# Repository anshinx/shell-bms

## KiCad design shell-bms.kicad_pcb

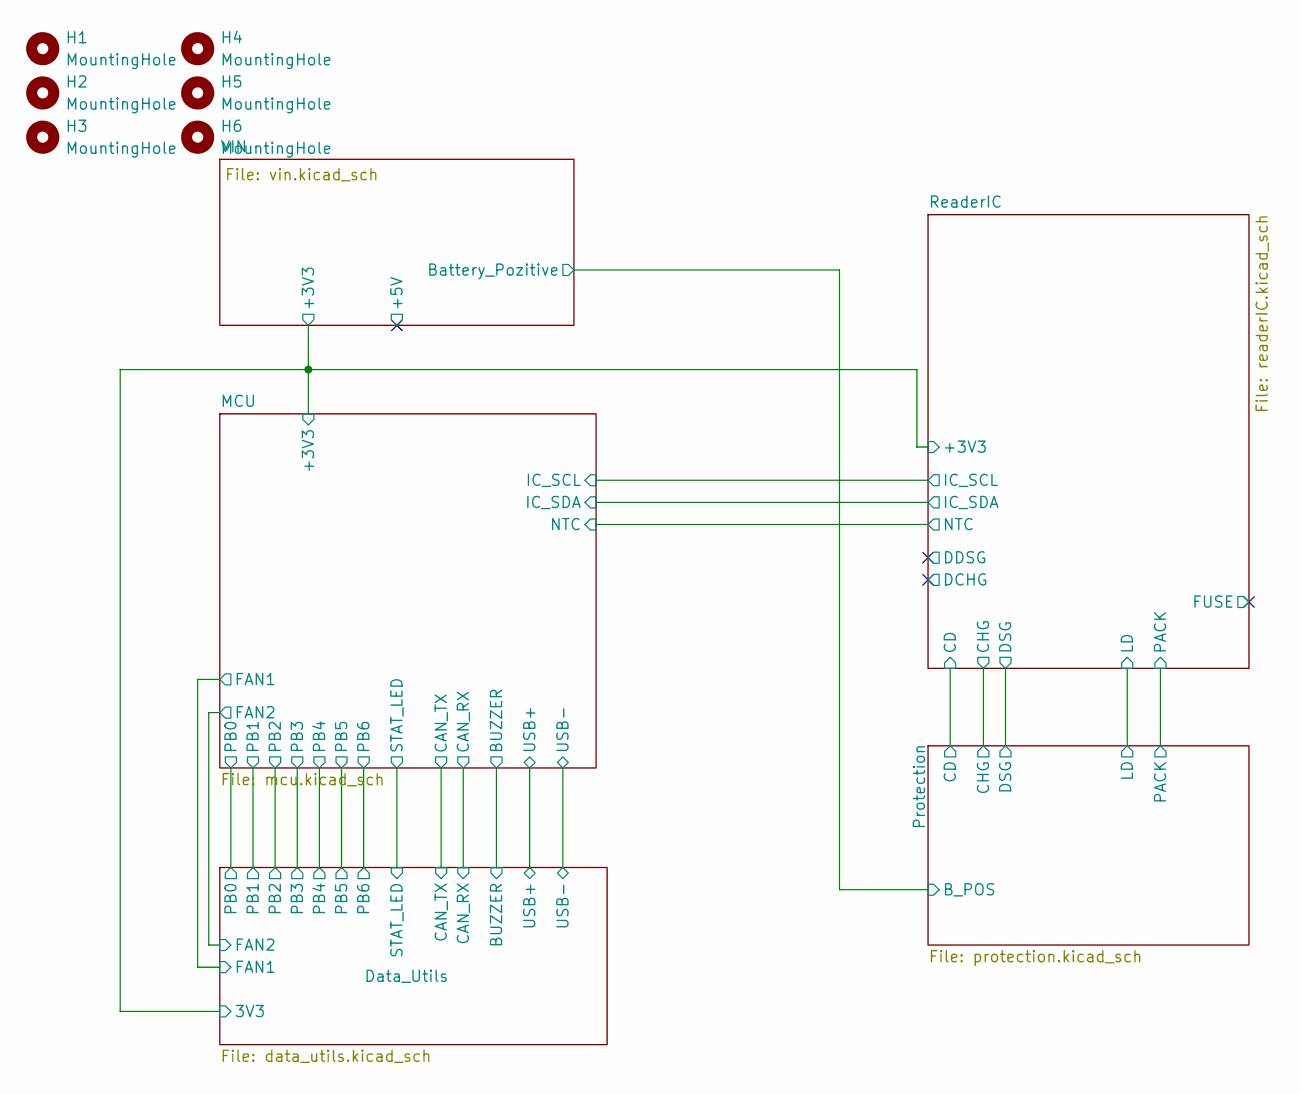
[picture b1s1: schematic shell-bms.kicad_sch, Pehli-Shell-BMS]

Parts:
H1, H2, H3, H4, H5, H6: MountingHole; Mounting_Wuerth_WA-SMST-2.25mm_H2.5mm_9774025943

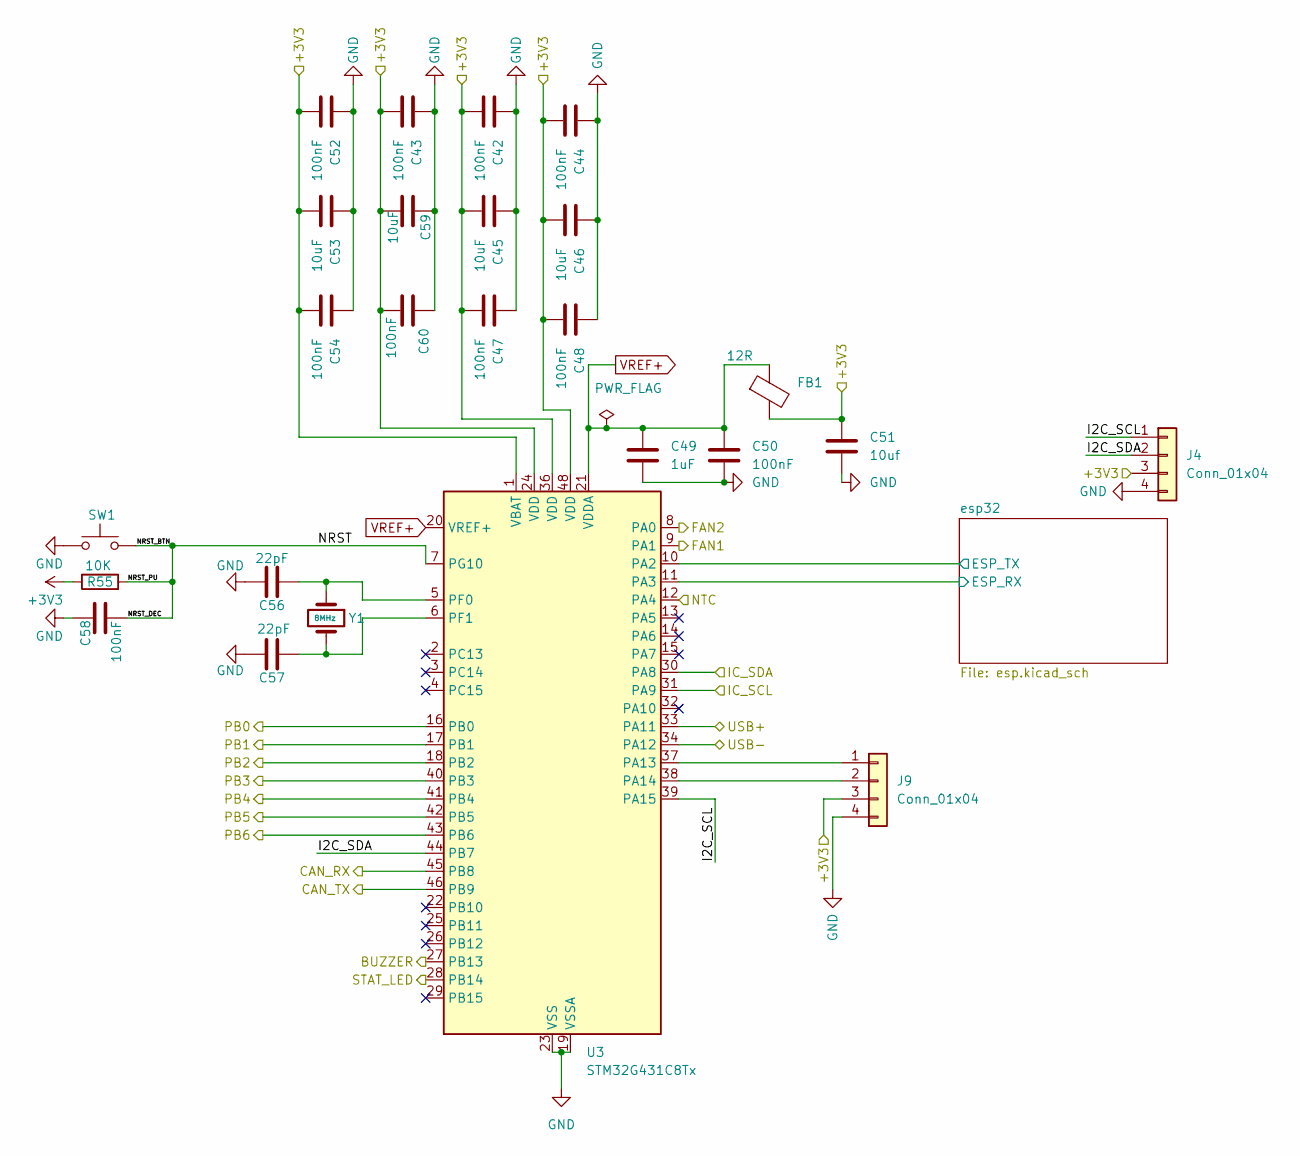
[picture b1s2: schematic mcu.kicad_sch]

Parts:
C42, C43, C44, C47, C48, C50, C52, C54, C60: 100nF; C_0603_1608Metric_Pad1.08x0.95mm_HandSolder
C45, C46, C53, C59: 10uF; C_0603_1608Metric_Pad1.08x0.95mm_HandSolder
C49: 1uF; C_0603_1608Metric_Pad1.08x0.95mm_HandSolder
C51: 10uf; C_0805_2012Metric_Pad1.18x1.45mm_HandSolder
C56, C57: 22pF; C_0603_1608Metric_Pad1.08x0.95mm_HandSolder
C58: 100nF; C_Disc_D10.5mm_W5.0mm_P5.00mm
FB1: 12R; R_0805_2012Metric_Pad1.20x1.40mm_HandSolder
J4, J9: Conn_01x04; PinSocket_1x04_P2.00mm_Vertical
R55: 10K; R_Axial_DIN0207_L6.3mm_D2.5mm_P7.62mm_Horizontal
SW1: SW_Push; SW_PUSH_6mm_H8mm
U3: STM32G431C8Tx; LQFP-48_7x7mm_P0.5mm
Y1: 8MHz; Crystal_HC18-U_Vertical

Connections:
+3V3: C42.2, C43.2, C44.2, C45.2, C46.2, C47.2, C48.2, C51.1, C52.2, C53.2, C54.2, C59.2, C60.2, FB1.2, J4.3, J9.3, R55.2, U3.1 (VBAT), U3.24 (VDD), U3.36 (VDD), U3.48 (VDD); also elsewhere on the board
/Data_Utils/BUZZER: U3.27 (PB13); also elsewhere on the board
/Data_Utils/CAN_RX: U3.45 (PB8); also elsewhere on the board
/Data_Utils/CAN_TX: U3.46 (PB9); also elsewhere on the board
/Data_Utils/FAN1: U3.9 (PA1); also elsewhere on the board
/Data_Utils/FAN2: U3.8 (PA0); also elsewhere on the board
/Data_Utils/PB0: U3.16 (PB0); also elsewhere on the board
/Data_Utils/PB1: U3.17 (PB1); also elsewhere on the board
/Data_Utils/PB2: U3.18 (PB2); also elsewhere on the board
/Data_Utils/PB3: U3.40 (PB3); also elsewhere on the board
/Data_Utils/PB4: U3.41 (PB4); also elsewhere on the board
/Data_Utils/PB5: U3.42 (PB5); also elsewhere on the board
/Data_Utils/PB6: U3.43 (PB6); also elsewhere on the board
/Data_Utils/STAT_LED: U3.28 (PB14); also elsewhere on the board
/Data_Utils/USB+: U3.33 (PA11); also elsewhere on the board
/Data_Utils/USB-: U3.34 (PA12); also elsewhere on the board
/MCU/I2C_SCL: J4.1, U3.39 (PA15)
/MCU/I2C_SDA: J4.2, U3.44 (PB7)
/MCU/IC_SCL: U3.31 (PA9); also elsewhere on the board
/MCU/IC_SDA: U3.30 (PA8); also elsewhere on the board
/MCU/NRST: C58.2, R55.1, SW1.2, U3.7 (PG10)
/MCU/NTC: U3.12 (PA4); also elsewhere on the board
/MCU/esp32/ESP_RX: U3.11 (PA3); also elsewhere on the board
/MCU/esp32/ESP_TX: U3.10 (PA2); also elsewhere on the board
GND: C42.1, C43.1, C44.1, C45.1, C46.1, C47.1, C48.1, C49.2, C50.2, C51.2, C52.1, C53.1, C54.1, C56.1, C57.1, C58.1, C59.1, C60.1, J4.4, J9.4, SW1.1, U3.19 (VSSA), U3.23 (VSS), U3.35 (VSS), U3.47 (VSS); also elsewhere on the board
unnamed: J9.1, U3.37 (PA13)
unnamed: J9.2, U3.38 (PA14)
unnamed: C56.2, U3.5 (PF0), Y1.1
unnamed: C57.2, U3.6 (PF1), Y1.2
VREF+: C49.1, C50.1, FB1.1, U3.20 (VREF+), U3.21 (VDDA)

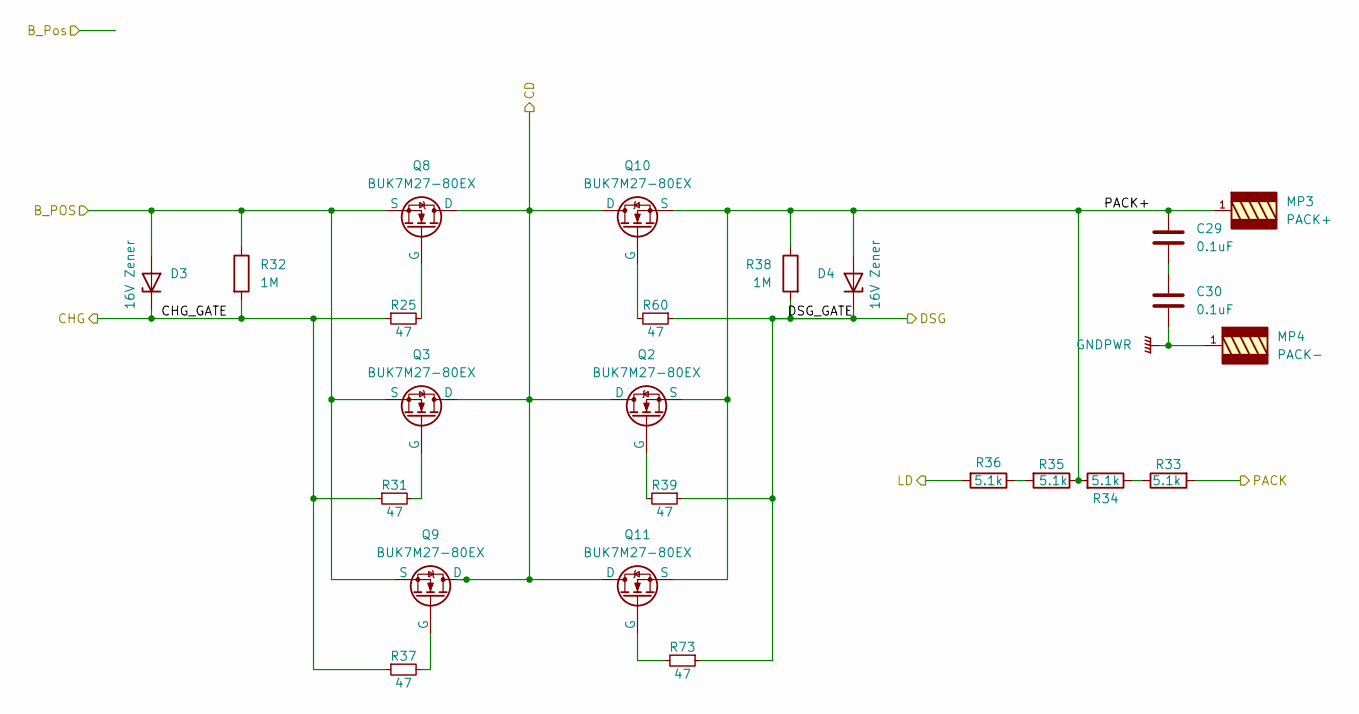
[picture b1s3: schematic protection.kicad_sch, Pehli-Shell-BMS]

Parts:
C29, C30: 0.1uF; C_0805_2012Metric_Pad1.18x1.45mm_HandSolder
D3, D4: 16V Zener; D_SMF
MP3: PACK+; WP-BUTR_7460307
MP4: PACK-; WP-BUTR_7460307
Q2, Q3, Q8, Q9, Q10, Q11: BUK7M27-80EX; LFPAK33
R25, R31, R37, R39, R60, R73: 47; R_0603_1608Metric_Pad0.98x0.95mm_HandSolder; PartNumber RC0603FR-0747RL
R32, R38: 1M; R_2512_6332Metric_Pad1.40x3.35mm_HandSolder
R33, R34, R35, R36: 5.1k; R_0603_1608Metric_Pad0.98x0.95mm_HandSolder

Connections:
/Protection/B_POS: D3.2 (A), Q3.1 (S), Q3.2 (S), Q3.3 (S), Q8.1 (S), Q8.2 (S), Q8.3 (S), Q9.1 (S), Q9.2 (S), Q9.3 (S), R32.1; also elsewhere on the board
/Protection/CD: Q2.5 (D), Q3.5 (D), Q8.5 (D), Q9.5 (D), Q10.5 (D), Q11.5 (D); also elsewhere on the board
/Protection/CHG_GATE: D3.1 (K), R25.1, R31.1, R32.2, R37.1; also elsewhere on the board
/Protection/DSG_GATE: D4.1 (K), R38.2, R39.1, R60.1, R73.1; also elsewhere on the board
/Protection/LD: R36.2; also elsewhere on the board
/Protection/PACK: R33.2; also elsewhere on the board
/Protection/PACK+: C29.1, D4.2 (A), MP3.1, MP3.2, MP3.3, MP3.4, MP3.5, MP3.6, MP3.7, MP3.8, Q2.1 (S), Q2.2 (S), Q2.3 (S), Q10.1 (S), Q10.2 (S), Q10.3 (S), Q11.1 (S), Q11.2 (S), Q11.3 (S), R34.2, R35.1, R38.1
GNDPWR: C30.2, MP4.1, MP4.2, MP4.3, MP4.4, MP4.5, MP4.6, MP4.7, MP4.8; also elsewhere on the board
unnamed: C29.2, C30.1
unnamed: Q2.4 (G), R39.2
unnamed: Q3.4 (G), R31.2
unnamed: Q8.4 (G), R25.2
unnamed: Q9.4 (G), R37.2
unnamed: Q10.4 (G), R60.2
unnamed: Q11.4 (G), R73.2
unnamed: R33.1, R34.1
unnamed: R35.2, R36.1

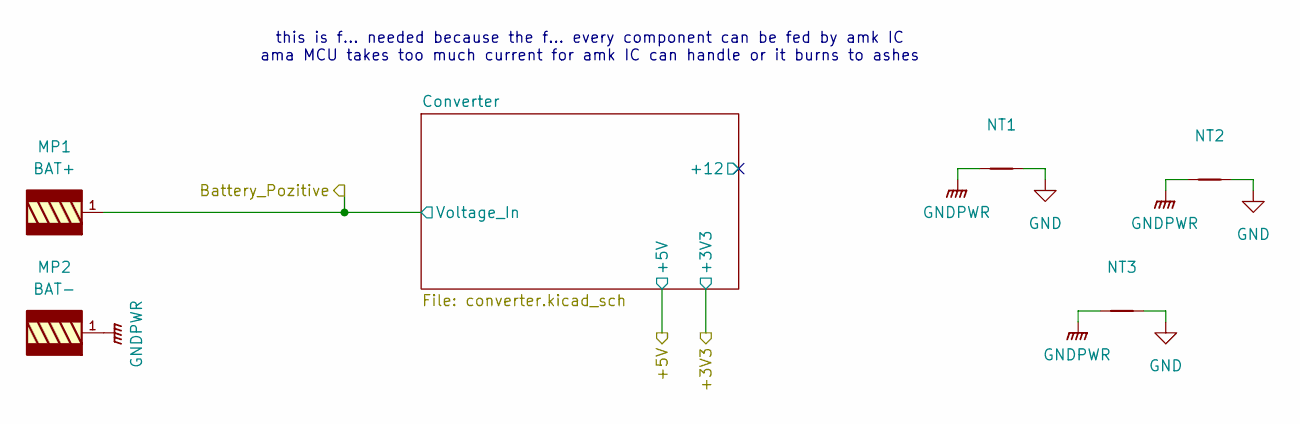
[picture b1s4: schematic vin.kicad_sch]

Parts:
MP1: BAT+; WP-BUTR_7460307
MP2: BAT-; WP-BUTR_7460307
NT1, NT2, NT3: NetTie_2; NetTie-2_THT_Pad0.3mm

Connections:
/Protection/B_POS: MP1.1, MP1.2, MP1.3, MP1.4, MP1.5, MP1.6, MP1.7, MP1.8; also elsewhere on the board
GND: NT1.2, NT2.2, NT3.2; also elsewhere on the board
GNDPWR: MP2.1, MP2.2, MP2.3, MP2.4, MP2.5, MP2.6, MP2.7, MP2.8, NT1.1, NT2.1, NT3.1; also elsewhere on the board

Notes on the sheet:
this is f... needed because the f... every component can be fed by amk IC ama MCU takes too much current for amk IC can handle or it burns to ashes

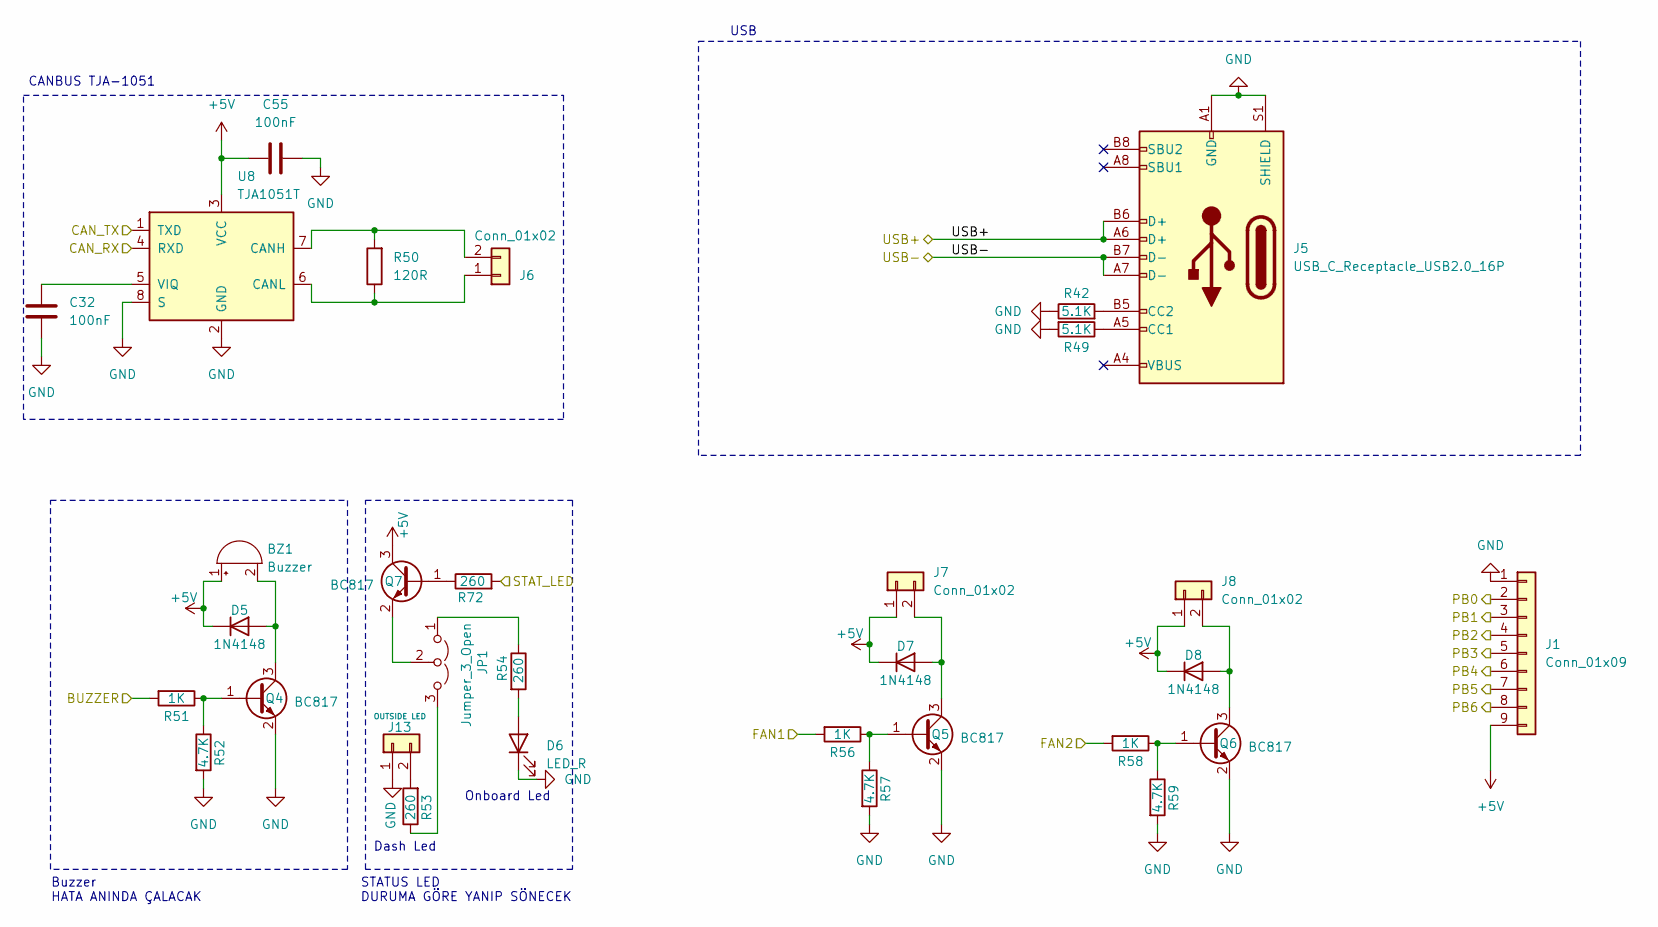
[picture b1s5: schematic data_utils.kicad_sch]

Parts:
BZ1: Buzzer; Buzzer_12x9.5RM7.6
C32: 100nF; C_0603_1608Metric_Pad1.08x0.95mm_HandSolder
C55: 100nF; C_1210_3225Metric_Pad1.33x2.70mm_HandSolder
D5, D7, D8: 1N4148; D_DO-35_SOD27_P7.62mm_Horizontal
D6: LED_R; LED_D1.8mm_W3.3mm_H2.4mm
J1: Conn_01x09; PinSocket_1x09_P2.54mm_Vertical
J5: USB_C_Receptacle_USB2.0_16P; USB_C_Receptacle_HCTL_HC-TYPE-C-16P-01A
J6: Conn_01x02; PinSocket_1x02_P2.00mm_Horizontal
J7, J8: Conn_01x02; PinSocket_1x02_P2.00mm_Vertical
J13: OUTSIDE LED; PinSocket_1x02_P2.00mm_Horizontal
JP1: Jumper_3_Open; PinHeader_1x03_P1.27mm_Vertical
Q4, Q5, Q6, Q7: BC817; SOT-23
R42, R49: 5.1K; R_0603_1608Metric_Pad0.98x0.95mm_HandSolder
R50: 120R; R_0603_1608Metric_Pad0.98x0.95mm_HandSolder
R51, R56, R58: 1K; R_1210_3225Metric_Pad1.30x2.65mm_HandSolder
R52, R57, R59: 4.7K; R_1210_3225Metric_Pad1.30x2.65mm_HandSolder
R53, R54, R72: 260; R_1210_3225Metric_Pad1.30x2.65mm_HandSolder
U8: TJA1051T; SOIC-8_3.9x4.9mm_P1.27mm

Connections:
+5V: BZ1.1 (+), C55.1, D5.1 (K), D7.1 (K), D8.1 (K), J1.9, J7.1, J8.1, Q7.3 (C), U8.3 (VCC); also elsewhere on the board
/Data_Utils/BUZZER: R51.2; also elsewhere on the board
/Data_Utils/CAN_RX: U8.4 (RXD); also elsewhere on the board
/Data_Utils/CAN_TX: U8.1 (TXD); also elsewhere on the board
/Data_Utils/FAN1: R56.2; also elsewhere on the board
/Data_Utils/FAN2: R58.2; also elsewhere on the board
/Data_Utils/PB0: J1.2; also elsewhere on the board
/Data_Utils/PB1: J1.3; also elsewhere on the board
/Data_Utils/PB2: J1.4; also elsewhere on the board
/Data_Utils/PB3: J1.5; also elsewhere on the board
/Data_Utils/PB4: J1.6; also elsewhere on the board
/Data_Utils/PB5: J1.7; also elsewhere on the board
/Data_Utils/PB6: J1.8; also elsewhere on the board
/Data_Utils/STAT_LED: R72.2; also elsewhere on the board
/Data_Utils/USB+: J5.A6 (D+), J5.B6 (D+); also elsewhere on the board
/Data_Utils/USB-: J5.A7 (D-), J5.B7 (D-); also elsewhere on the board
GND: C32.2, C55.2, D6.1 (K), J1.1, J5.A1 (GND), J5.A12 (GND), J5.B1 (GND), J5.B12 (GND), J5.S1 (SHIELD), J13.1, Q4.2 (E), Q5.2 (E), Q6.2 (E), R42.1, R49.2, R52.2, R57.2, R59.2, U8.2 (GND), U8.8 (S); also elsewhere on the board
unnamed: BZ1.2 (-), D5.2 (A), Q4.3 (C)
unnamed: D6.2 (A), R54.2
unnamed: D7.2 (A), J7.2, Q5.3 (C)
unnamed: D8.2 (A), J8.2, Q6.3 (C)
unnamed: J5.A5 (CC1), R49.1
unnamed: J5.B5 (CC2), R42.2
unnamed: J6.1, R50.1, U8.6 (CANL)
unnamed: J6.2, R50.2, U8.7 (CANH)
unnamed: J13.2, R53.2
unnamed: JP1.1 (A), R54.1
unnamed: JP1.3 (B), R53.1
unnamed: JP1.2 (C), Q7.2 (E)
unnamed: Q4.1 (B), R51.1, R52.1
unnamed: Q5.1 (B), R56.1, R57.1
unnamed: Q6.1 (B), R58.1, R59.1
unnamed: Q7.1 (B), R72.1
unnamed: C32.1, U8.5 (VIQ)

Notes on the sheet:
Buzzer HATA ANINDA ÇALACAK
CANBUS TJA-1051
STATUS LED DURUMA GÖRE YANIP SÖNECEK
USB
Dash Led
Onboard Led

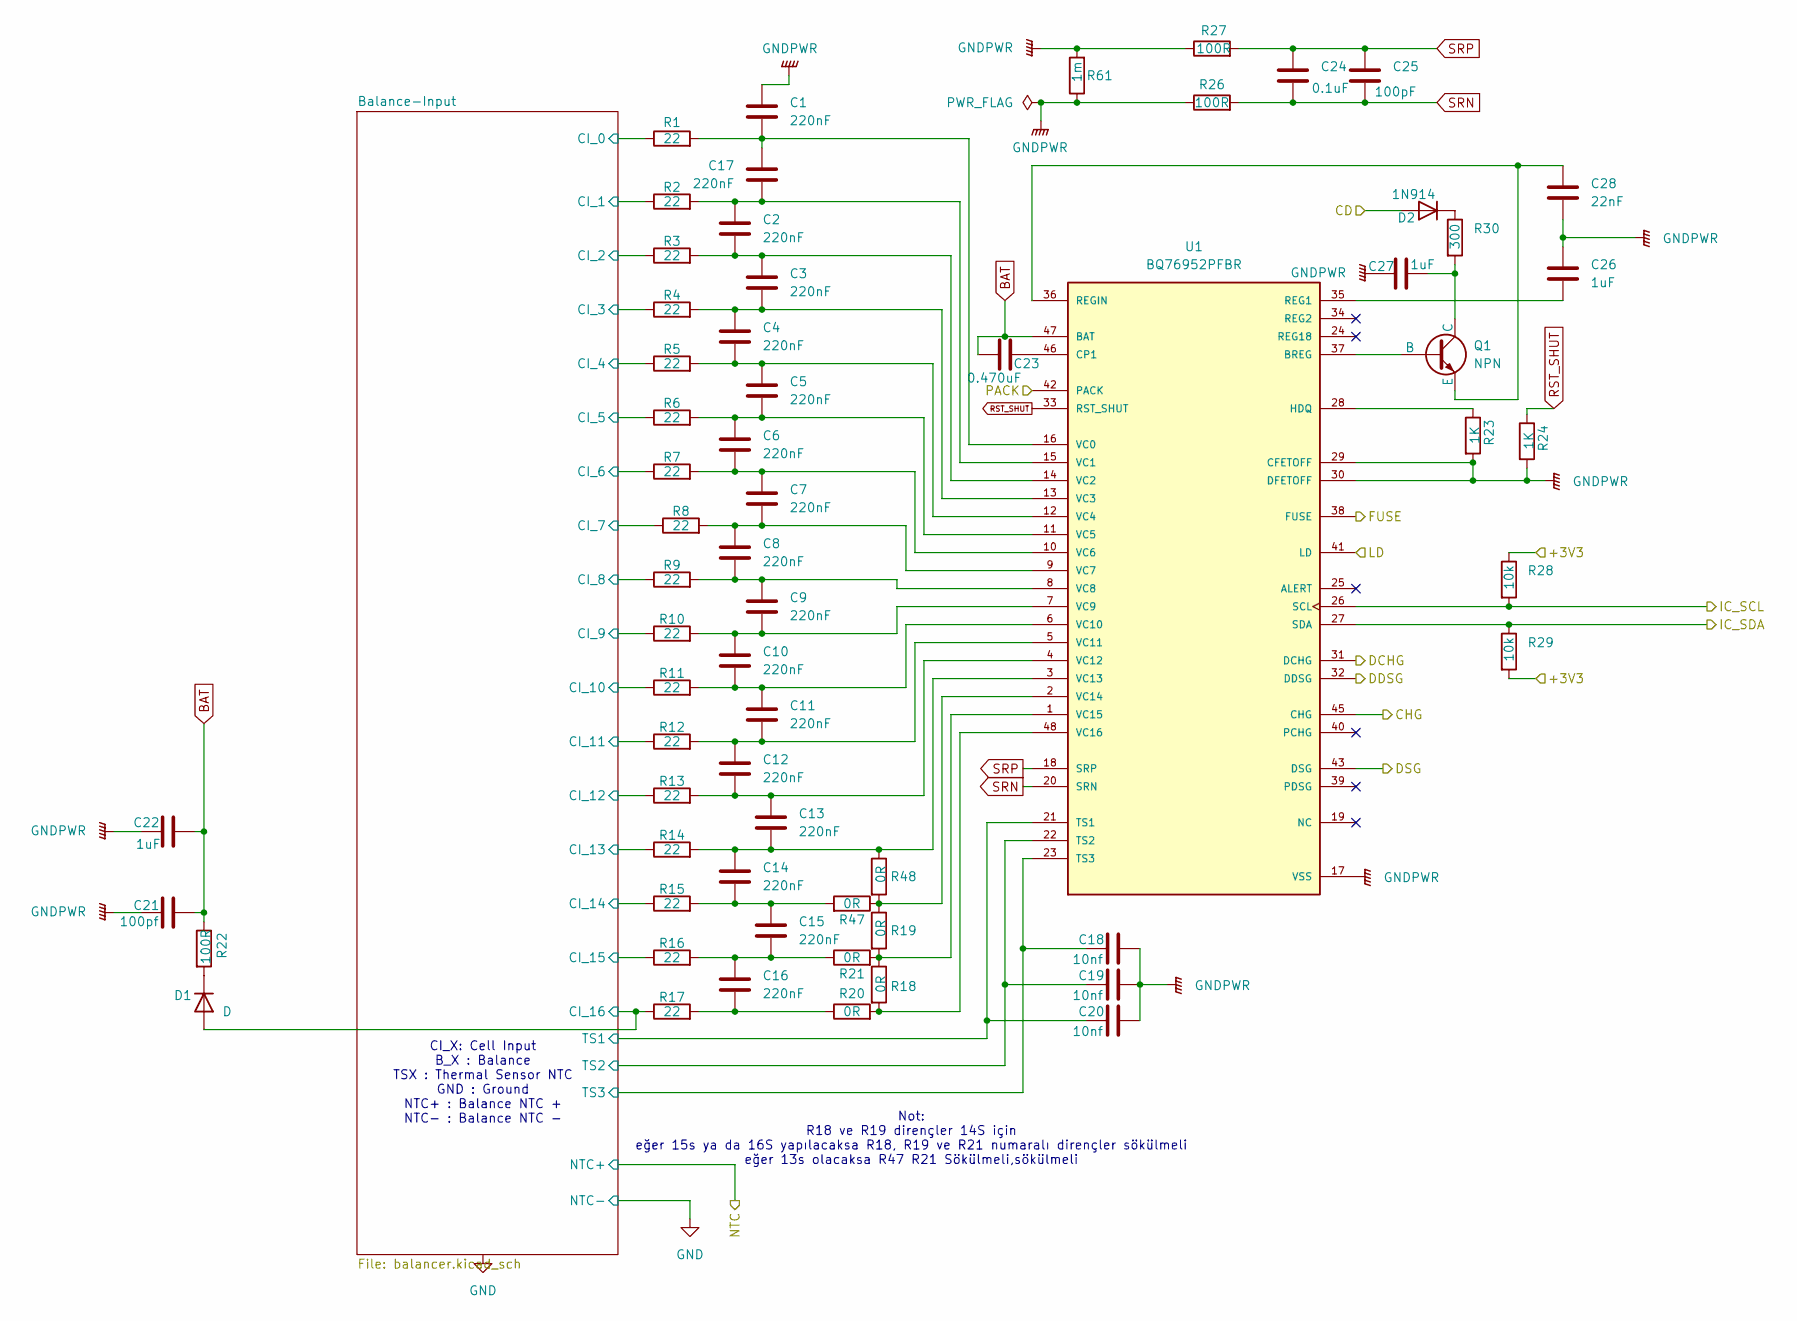
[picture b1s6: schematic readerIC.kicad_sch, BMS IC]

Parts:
C1, C2, C3, C4, C5, C6, C7, C8, C9, C10, C11, C12, C13, C14, C15, C16, C17: 220nF; C_0805_2012Metric_Pad1.18x1.45mm_HandSolder
C18, C19, C20: 10nf; C_1210_3225Metric_Pad1.33x2.70mm_HandSolder
C21: 100pf; C_0805_2012Metric_Pad1.18x1.45mm_HandSolder
C22, C26, C27: 1uF; C_0805_2012Metric_Pad1.18x1.45mm_HandSolder
C23: 0.470uF; C_0805_2012Metric_Pad1.18x1.45mm_HandSolder
C24: 0.1uF; C_0805_2012Metric_Pad1.18x1.45mm_HandSolder
C25: 100pF; C_0805_2012Metric_Pad1.18x1.45mm_HandSolder
C28: 22nF; C_0805_2012Metric_Pad1.18x1.45mm_HandSolder
D1: D; D_A-405_P7.62mm_Horizontal
D2: 1N914; D_DO-35_SOD27_P7.62mm_Horizontal
Q1: NPN; TO-92_HandSolder
R1, R2, R3, R4, R5, R6, R7, R8, R9, R10, R11, R12, R13, R14, R15, R16, R17: 22; R_1210_3225Metric_Pad1.30x2.65mm_HandSolder
R18, R19, R20, R21, R47, R48: 0R; R_0603_1608Metric_Pad0.98x0.95mm_HandSolder
R22: 100R; R_Axial_DIN0309_L9.0mm_D3.2mm_P15.24mm_Horizontal
R23, R24: 1K; R_0603_1608Metric_Pad0.98x0.95mm_HandSolder
R26, R27: 100R; R_0603_1608Metric_Pad0.98x0.95mm_HandSolder
R28, R29: 10k; R_0603_1608Metric_Pad0.98x0.95mm_HandSolder
R30: 300; R_0805_2012Metric_Pad1.20x1.40mm_HandSolder
R61: 1m; R_1210_3225Metric_Pad1.30x2.65mm_HandSolder
U1: BQ76952PFBR; QFP50P900X900X120-48N; PARTREV B

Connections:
+3V3: R28.1, R29.2; also elsewhere on the board
/MCU/IC_SCL: R28.2, U1.26 (SCL); also elsewhere on the board
/MCU/IC_SDA: R29.1, U1.27 (SDA); also elsewhere on the board
/Protection/CD: D2.2 (A); also elsewhere on the board
/Protection/CHG_GATE: U1.45 (CHG); also elsewhere on the board
/Protection/DSG_GATE: U1.43 (DSG); also elsewhere on the board
/Protection/LD: U1.41 (LD); also elsewhere on the board
/Protection/PACK: U1.42 (PACK); also elsewhere on the board
/ReaderIC/Balance-Input/CI_0: R1.1; also elsewhere on the board
/ReaderIC/Balance-Input/CI_1: R2.1; also elsewhere on the board
/ReaderIC/Balance-Input/CI_2: R3.1; also elsewhere on the board
/ReaderIC/Balance-Input/CI_3: R4.1; also elsewhere on the board
/ReaderIC/Balance-Input/CI_4: R5.1; also elsewhere on the board
/ReaderIC/Balance-Input/CI_5: R6.1; also elsewhere on the board
/ReaderIC/Balance-Input/CI_6: R7.1; also elsewhere on the board
/ReaderIC/Balance-Input/CI_7: R8.1; also elsewhere on the board
/ReaderIC/Balance-Input/CI_8: R9.1; also elsewhere on the board
/ReaderIC/Balance-Input/CI_9: R10.1; also elsewhere on the board
/ReaderIC/Balance-Input/CI_10: R11.1; also elsewhere on the board
/ReaderIC/Balance-Input/CI_11: R12.1; also elsewhere on the board
/ReaderIC/Balance-Input/CI_12: R13.1; also elsewhere on the board
/ReaderIC/Balance-Input/CI_13: R14.1; also elsewhere on the board
/ReaderIC/Balance-Input/CI_14: R15.1; also elsewhere on the board
/ReaderIC/Balance-Input/CI_15: R16.1; also elsewhere on the board
/ReaderIC/Balance-Input/CI_16: D1.2 (A), R17.1; also elsewhere on the board
/ReaderIC/Balance-Input/TS1: C20.1, U1.21 (TS1); also elsewhere on the board
/ReaderIC/Balance-Input/TS2: C19.1, U1.22 (TS2); also elsewhere on the board
/ReaderIC/Balance-Input/TS3: C18.1, U1.23 (TS3); also elsewhere on the board
/ReaderIC/DCHG: U1.31 (DCHG)
/ReaderIC/DDSG: U1.32 (DDSG)
/ReaderIC/FUSE: U1.38 (FUSE)
BAT: C21.2, C22.2, C23.1, R22.1, U1.47 (BAT)
GNDPWR: C1.1, C18.2, C19.2, C20.2, C21.1, C22.1, C26.2, C27.1, C28.1, R23.2, R24.2, R26.1, R27.1, R61.1, R61.2, U1.17 (VSS), U1.29 (CFETOFF), U1.30 (DFETOFF); also elsewhere on the board
unnamed: C14.2, C15.1, R15.2, R47.2
unnamed: C15.2, C16.1, R16.2, R21.1
unnamed: C16.2, R17.2, R20.1
unnamed: D1.1 (K), R22.2
unnamed: D2.1 (K), R30.1
unnamed: Q1.2 (B), U1.37 (BREG)
unnamed: C27.2, Q1.1 (C), R30.2
unnamed: C28.2, Q1.3 (E), U1.36 (REGIN)
unnamed: C23.2, U1.46 (CP1)
unnamed: R23.1, U1.28 (HDQ)
unnamed: C26.1, U1.35 (REG1)
unnamed: C1.2, C17.1, R1.2, U1.16 (VC0)
unnamed: C2.1, C17.2, R2.2, U1.15 (VC1)
unnamed: C2.2, C3.1, R3.2, U1.14 (VC2)
unnamed: C3.2, C4.2, R4.2, U1.13 (VC3)
unnamed: C4.1, C5.1, R5.2, U1.12 (VC4)
unnamed: C5.2, C6.1, R6.2, U1.11 (VC5)
unnamed: C6.2, C7.1, R7.2, U1.10 (VC6)
unnamed: C7.2, C8.1, R8.2, U1.9 (VC7)
unnamed: C8.2, C9.1, R9.2, U1.8 (VC8)
unnamed: C9.2, C10.1, R10.2, U1.7 (VC9)
unnamed: C10.2, C11.1, R11.2, U1.6 (VC10)
unnamed: C11.2, C12.1, R12.2, U1.5 (VC11)
unnamed: C12.2, C13.1, R13.2, U1.4 (VC12)
unnamed: C13.2, C14.1, R14.2, R48.1, U1.3 (VC13)
unnamed: R19.1, R47.1, R48.2, U1.2 (VC14)
unnamed: R18.1, R19.2, R21.2, U1.1 (VC15)
unnamed: R18.2, R20.2, U1.48 (VC16)
RST_SHUT: R24.1, U1.33 (RST_SHUT)
SRN: C24.2, C25.2, R26.2, U1.20 (SRN)
SRP: C24.1, C25.1, R27.2, U1.18 (SRP)

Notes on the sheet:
Not: R18 ve R19 dirençler 14S için eğer 15s ya da 16S yapılacaksa R18, R19 ve R21 numaralı dirençler sökülmeli eğer 13s olacaksa R47 R21 Sökülmeli,sökülmeli
CI_X: Cell Input B_X : Balance TSX : Thermal Sensor NTC GND : Ground NTC+ : Balance NTC + NTC- : Balance NTC -

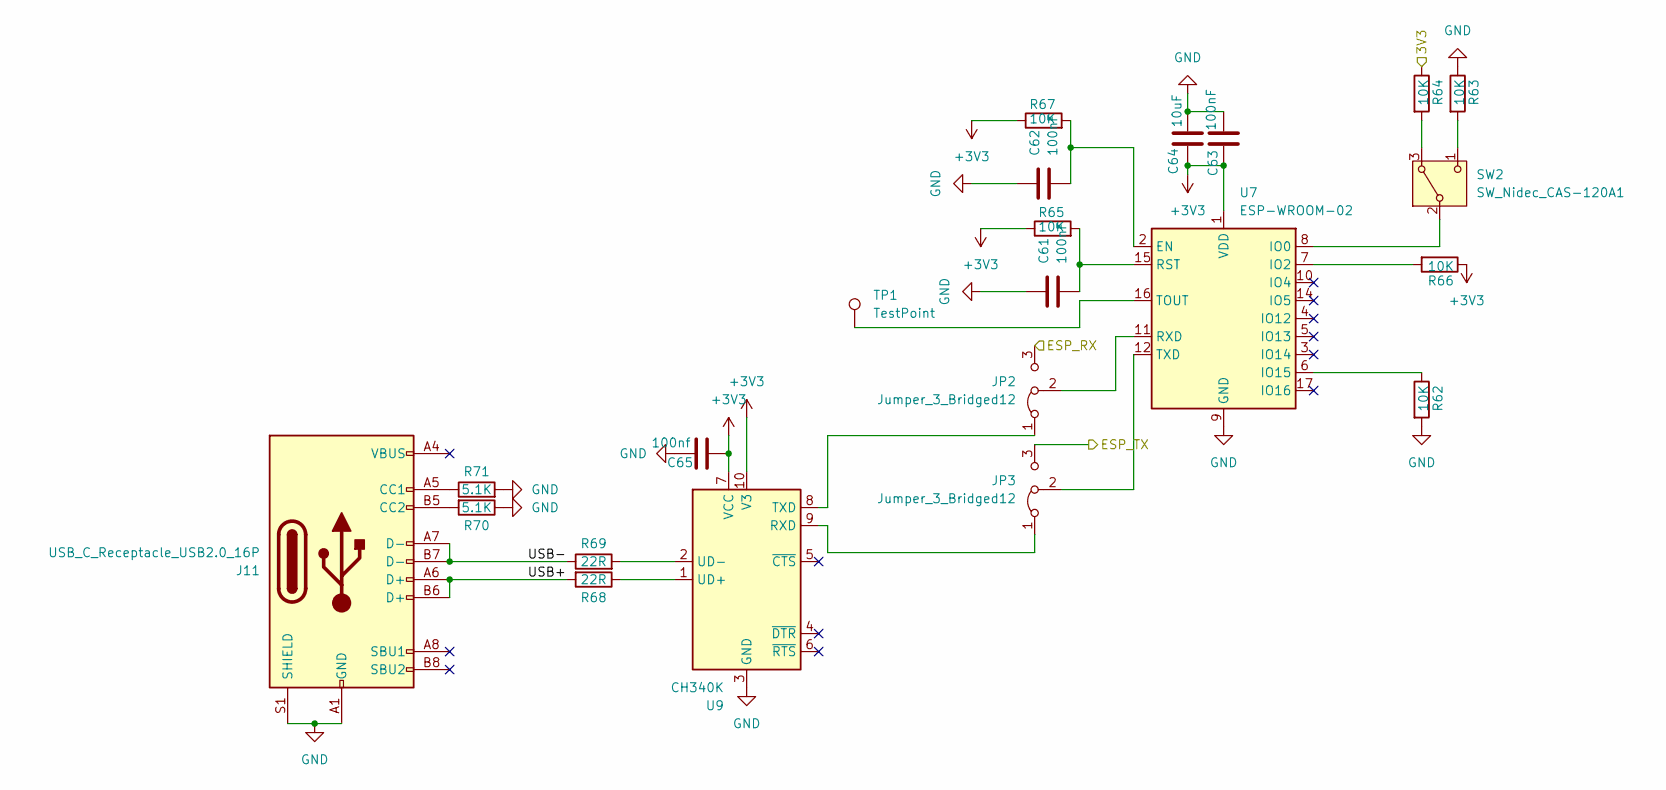
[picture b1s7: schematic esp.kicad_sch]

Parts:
C61, C62, C63: 100nF; C_0603_1608Metric_Pad1.08x0.95mm_HandSolder
C64: 10uF; C_0603_1608Metric_Pad1.08x0.95mm_HandSolder
C65: 100nf; C_0805_2012Metric_Pad1.18x1.45mm_HandSolder
J11: USB_C_Receptacle_USB2.0_16P; USB_C_Receptacle_HCTL_HC-TYPE-C-16P-01A
JP2, JP3: Jumper_3_Bridged12; SolderJumper-3_P1.3mm_Bridged2Bar12_Pad1.0x1.5mm
R62, R63, R64, R65, R66, R67: 10K; R_0612_1632Metric_Pad1.18x3.40mm_HandSolder
R68, R69: 22R; R_0603_1608Metric_Pad0.98x0.95mm_HandSolder
R70, R71: 5.1K; R_0603_1608Metric_Pad0.98x0.95mm_HandSolder
SW2: SW_Nidec_CAS-120A1; Nidec_Copal_CAS-120A
TP1: TestPoint; TestPoint_Loop_D2.50mm_Drill1.0mm_LowProfile
U7: ESP-WROOM-02
U9: CH340K; SSOP-10-1EP_3.9x4.9mm_P1mm_EP2.1x3.3mm

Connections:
+3V3: C63.2, C64.2, C65.1, R65.1, R66.1, R67.1, U7.1 (VDD), U9.7 (VCC), U9.10 (V3); also elsewhere on the board
/MCU/esp32/3V3: R64.1
/MCU/esp32/ESP_RX: JP2.3 (B); also elsewhere on the board
/MCU/esp32/ESP_TX: JP3.3 (B); also elsewhere on the board
/MCU/esp32/USB+: J11.A6 (D+), J11.B6 (D+), R68.2
/MCU/esp32/USB-: J11.A7 (D-), J11.B7 (D-), R69.1
GND: C61.2, C62.2, C63.1, C64.1, C65.2, J11.A1 (GND), J11.A12 (GND), J11.B1 (GND), J11.B12 (GND), J11.S1 (SHIELD), R62.2, R63.1, R70.1, R71.2, U7.9 (GND), U7.13 (GND), U7.18 (GND), U7.19 (GND), U9.3 (GND), U9.11 (GND); also elsewhere on the board
unnamed: J11.A5 (CC1), R71.1
unnamed: J11.B5 (CC2), R70.2
unnamed: JP2.1 (A), U9.8 (TXD)
unnamed: JP2.2 (C), U7.11 (RXD)
unnamed: JP3.1 (A), U9.9 (RXD)
unnamed: JP3.2 (C), U7.12 (TXD)
unnamed: R64.2, SW2.3 (A)
unnamed: SW2.2 (B), U7.8 (IO0)
unnamed: R63.2, SW2.1 (C)
unnamed: C62.1, R67.2, U7.2 (EN)
unnamed: R66.2, U7.7 (IO2)
unnamed: R62.1, U7.6 (IO15)
unnamed: C61.1, R65.2, U7.15 (RST)
unnamed: TP1.1, U7.16 (TOUT)
unnamed: R68.1, U9.1 (UD+)
unnamed: R69.2, U9.2 (UD-)

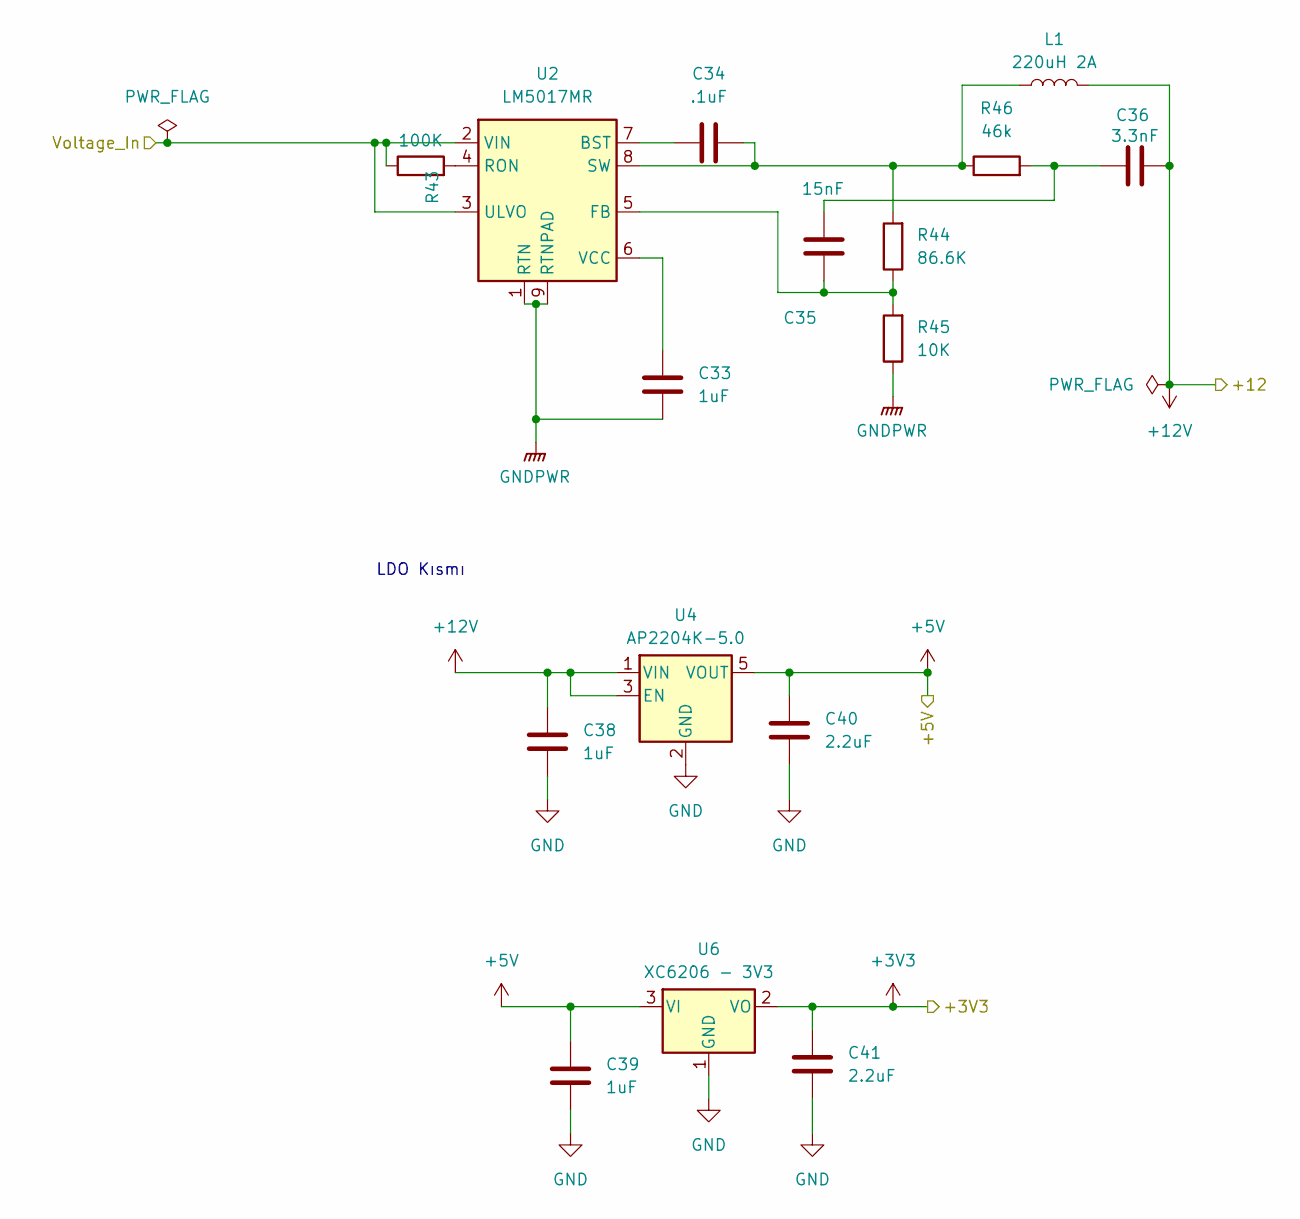
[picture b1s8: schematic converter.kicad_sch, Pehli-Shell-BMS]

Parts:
C33: 1uF; C_1210_3225Metric_Pad1.33x2.70mm_HandSolder
C34: .1uF; C_0603_1608Metric_Pad1.08x0.95mm_HandSolder
C35: 15nF; C_0603_1608Metric_Pad1.08x0.95mm_HandSolder
C36: 3.3nF; C_0603_1608Metric_Pad1.08x0.95mm_HandSolder
C38, C39: 1uF; C_0603_1608Metric_Pad1.08x0.95mm_HandSolder
C40, C41: 2.2uF; C_0603_1608Metric_Pad1.08x0.95mm_HandSolder
L1: 220uH 2A; L_1210_3225Metric_Pad1.42x2.65mm_HandSolder
R43: 100K; R_0603_1608Metric_Pad0.98x0.95mm_HandSolder
R44: 86.6K; R_0603_1608Metric_Pad0.98x0.95mm_HandSolder
R45: 10K; R_0603_1608Metric_Pad0.98x0.95mm_HandSolder
R46: 46k; R_0603_1608Metric_Pad0.98x0.95mm_HandSolder
U2: LM5017MR; SOIC-8-1EP_3.9x4.9mm_P1.27mm_EP2.95x4.9mm_Mask2.71x3.4mm_Th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
U4: AP2204K-5.0; SOT-23-5
U6: XC6206 - 3V3; SOT-23-3

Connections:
+3V3: C41.1, U6.2 (VO); also elsewhere on the board
+5V: C39.1, C40.1, U4.5 (VOUT), U6.3 (VI); also elsewhere on the board
+12V: C36.2, C38.1, L1.2, U4.1 (VIN), U4.3 (EN)
/Protection/B_POS: R43.1, U2.2 (VIN), U2.3 (ULVO); also elsewhere on the board
GND: C38.2, C39.2, C40.2, C41.2, U4.2 (GND), U6.1 (GND); also elsewhere on the board
GNDPWR: C33.2, R45.1, U2.1 (RTN), U2.9 (RTNPAD); also elsewhere on the board
unnamed: C35.2, C36.1, R46.2
unnamed: C34.1, U2.7 (BST)
unnamed: C35.1, R44.1, R45.2, U2.5 (FB)
unnamed: R43.2, U2.4 (RON)
unnamed: C34.2, L1.1, R44.2, R46.1, U2.8 (SW)
unnamed: C33.1, U2.6 (VCC)

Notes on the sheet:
LDO Kısmı

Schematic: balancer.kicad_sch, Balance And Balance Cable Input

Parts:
J2: Conn_01x20; Wago_734-180_1x20_P3.50mm_Horizontal
J3: Conn_01x04; PinSocket_1x04_P2.54mm_Vertical

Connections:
/MCU/NTC: J2.19; also elsewhere on the board
/ReaderIC/Balance-Input/CI_0: J2.17; also elsewhere on the board
/ReaderIC/Balance-Input/CI_1: J2.16; also elsewhere on the board
/ReaderIC/Balance-Input/CI_2: J2.15; also elsewhere on the board
/ReaderIC/Balance-Input/CI_3: J2.14; also elsewhere on the board
/ReaderIC/Balance-Input/CI_4: J2.13; also elsewhere on the board
/ReaderIC/Balance-Input/CI_5: J2.12; also elsewhere on the board
/ReaderIC/Balance-Input/CI_6: J2.11; also elsewhere on the board
/ReaderIC/Balance-Input/CI_7: J2.10; also elsewhere on the board
/ReaderIC/Balance-Input/CI_8: J2.9; also elsewhere on the board
/ReaderIC/Balance-Input/CI_9: J2.8; also elsewhere on the board
/ReaderIC/Balance-Input/CI_10: J2.7; also elsewhere on the board
/ReaderIC/Balance-Input/CI_11: J2.6; also elsewhere on the board
/ReaderIC/Balance-Input/CI_12: J2.5; also elsewhere on the board
/ReaderIC/Balance-Input/CI_13: J2.4; also elsewhere on the board
/ReaderIC/Balance-Input/CI_14: J2.3; also elsewhere on the board
/ReaderIC/Balance-Input/CI_15: J2.2; also elsewhere on the board
/ReaderIC/Balance-Input/CI_16: J2.1; also elsewhere on the board
/ReaderIC/Balance-Input/TS1: J3.1; also elsewhere on the board
/ReaderIC/Balance-Input/TS2: J3.2; also elsewhere on the board
/ReaderIC/Balance-Input/TS3: J3.3; also elsewhere on the board
GND: J2.20; also elsewhere on the board
GNDPWR: J3.4; also elsewhere on the board
